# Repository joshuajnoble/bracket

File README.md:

The Bracket
=======

This is, obviously, an art/critical design project more than something that you should build to try out. The shock mechanism I'm using is the flash from a disposable camera like [this](http://www.amazon.com/Disposable-Kodak-Camera-3Pack/dp/B000OFW65I/ref=sr_1_1?ie=UTF8&qid=1419345802&sr=8-1&keywords=Disposable-Kodak-Camera-3Pack) and is, seriously, quite painful. The OF application that is used to set the wearers income will be included here but is not at present, mostly because I haven't been able to build+test it against ios8 or any reasonably recent iPhone. It's very simple though and basically just leverages ofxBLE to show a prompt when it detects the bracket and send a message when the user enters an income.

Many thanks to @billautomata for the help with pulling census regions out of an SVG map

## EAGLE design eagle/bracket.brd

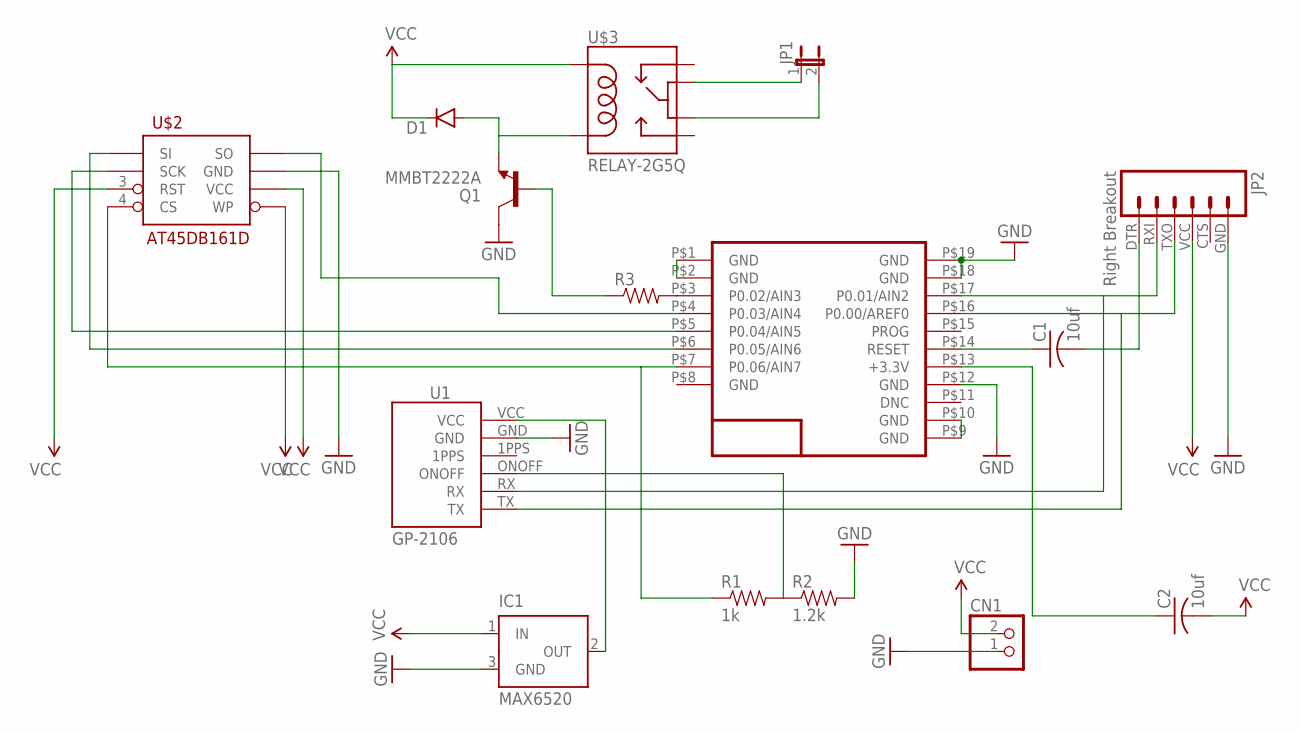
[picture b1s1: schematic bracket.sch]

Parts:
C1, C2: 10uf; C0603
CN1: JST_2PIN-SMT; JST-PH-2-SMT
D1: DIODESOD523; SOD523
IC1: MAX6520; SOT23
JP1: JP1E; JP1
JP2: Right Breakout; 1X06
Q1: MMBT2222A; SOT23-3
R1: 1k; 0603-RES
R2: 1.2k; 0603-RES
R3: RESISTOR0603-RES; 0603-RES
U1: GP-2106
U$1: RFD22301; RFD21733
U$2: AT45DB161D; SO08-EIAJ
U$3: RELAY-2G5Q; RELAY-G5V

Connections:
GND: CN1.1 (2), IC1.3 (GND), JP2.GND (6), Q1.3 (C), R2.2, U1.GND, U$1.P$12 (GND), U$1.P$18 (GND), U$1.P$19 (GND), U$2.7 (GND)
unnamed: JP2.RXI (2), U1.RX, U$1.P$17 (P0.01/AIN2)
unnamed: U$1.P$9 (GND), U$1.P$10 (GND)
unnamed: U$1.P$1 (GND), U$1.P$2 (GND)
unnamed: C1.1, U$1.P$14 (RESET)
unnamed: C1.2, JP2.DTR (1)
unnamed: JP2.TXO (3), U1.TX, U$1.P$16 (P0.00/AREF0)
unnamed: U$1.P$6 (P0.05/AIN6), U$2.1 (SI)
unnamed: U$1.P$4 (P0.03/AIN4), U$2.8 (SO)
unnamed: R3.2, U$1.P$3 (P0.02/AIN3)
unnamed: Q1.1 (B), R3.1
unnamed: D1.A, Q1.2 (E), U$3.9
unnamed: U$1.P$5 (P0.04/AIN5), U$2.2 (SCK)
unnamed: JP1.1, U$3.5
unnamed: JP1.2, U$3.6
unnamed: IC1.2 (OUT), U1.VCC
unnamed: R1.1, U$1.P$7 (P0.06/AIN7), U$2.4 (CS)
unnamed: C2.1, U$1.P$13 (+3.3V)
unnamed: R1.2, R2.1, U1.ONOFF
VCC: C2.2, CN1.2 (1), D1.C, IC1.1 (IN), JP2.VCC (4), U$2.3 (RST), U$2.5 (WP), U$2.6 (VCC), U$3.2

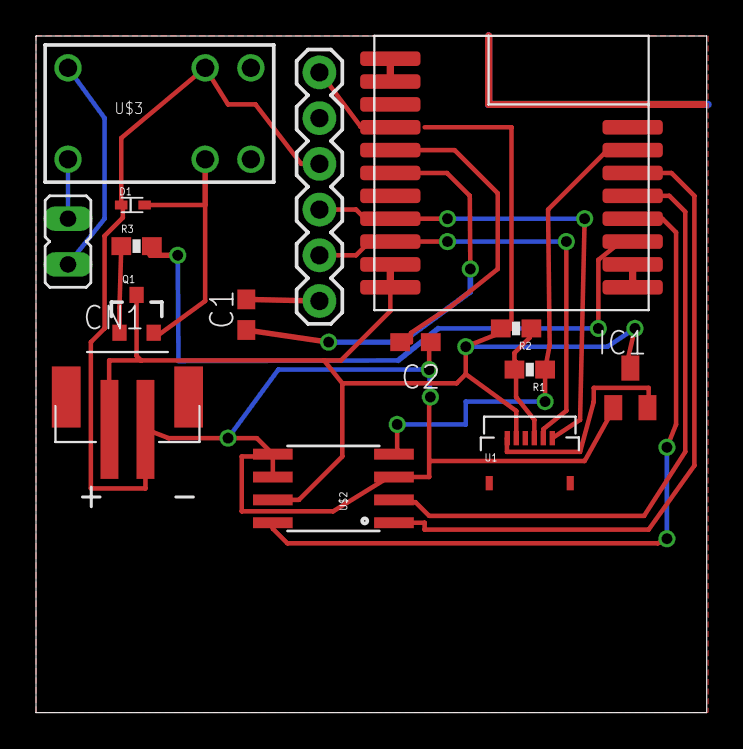
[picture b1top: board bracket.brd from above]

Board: 2 copper layers, 37.3 x 37.6 mm, 15 parts (0 on the bottom side), 20 nets.

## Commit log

2014-12-18 first commit:
2014-12-23 Fix amazon URL
2014-12-29 adding credit to billautomata
2015-07-11 updating board

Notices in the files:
parts and their libraries:
SparkFun-Connectors: Licensing: Creative Commons ShareAlike 4.0 International - https://creativecommons.org/licenses/by-sa/4.0
